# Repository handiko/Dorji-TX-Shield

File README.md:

# Arduino UNO Shield for Dorji DRA818V/U Transmitter
Dorji DRA818V VHF transmitter module shield for Arduino UNO &amp; compatibles.
This Arduino shield is intended to used as an APRS Transmitter module based on Arduino UNO (see my Arduino APRS [GitHub page](https://handiko.github.io/Arduino-APRS/) or [GitHub repo](https://github.com/handiko/Arduino-APRS). In this version (v.1.0), this board only support low power mode since high power will demand more current and this board only powered from 5V pin of the Arduino (It doesn't obtain power from Arduino Vin pin, yet).

## Photos

## Pinout

_Please note that in order to use PIN 8-11 as Serial Data lines, you need to use **SoftwareSerial** library._

## Schematic

## TODO
* Adding Silkscreen layer
* Adding ISP port capability
* Adding RX capability (maybe in a different repo..?)
* ...

## Acknowledgements
* Djoko Marjono Susilo - YB1TJ
* Adafruit Proto Shield PCB [GitHub page](https://github.com/adafruit/Adafruit-Proto-Shield-PCB)

## Contributing
1. Fork it [https://github.com/handiko/Dorji-TX-Shield/fork](https://github.com/handiko/Dorji-TX-Shield/fork)
2. Create new branch (`git checkout -b add-blah-blah`)
3. Do some editing / create new feature
4. Commit your works (`git commit -m "Adding some blah blah blah.."`)
5. Push to the branch (`git push -u origin add-blah-blah`)
6. Create a new Pull Request

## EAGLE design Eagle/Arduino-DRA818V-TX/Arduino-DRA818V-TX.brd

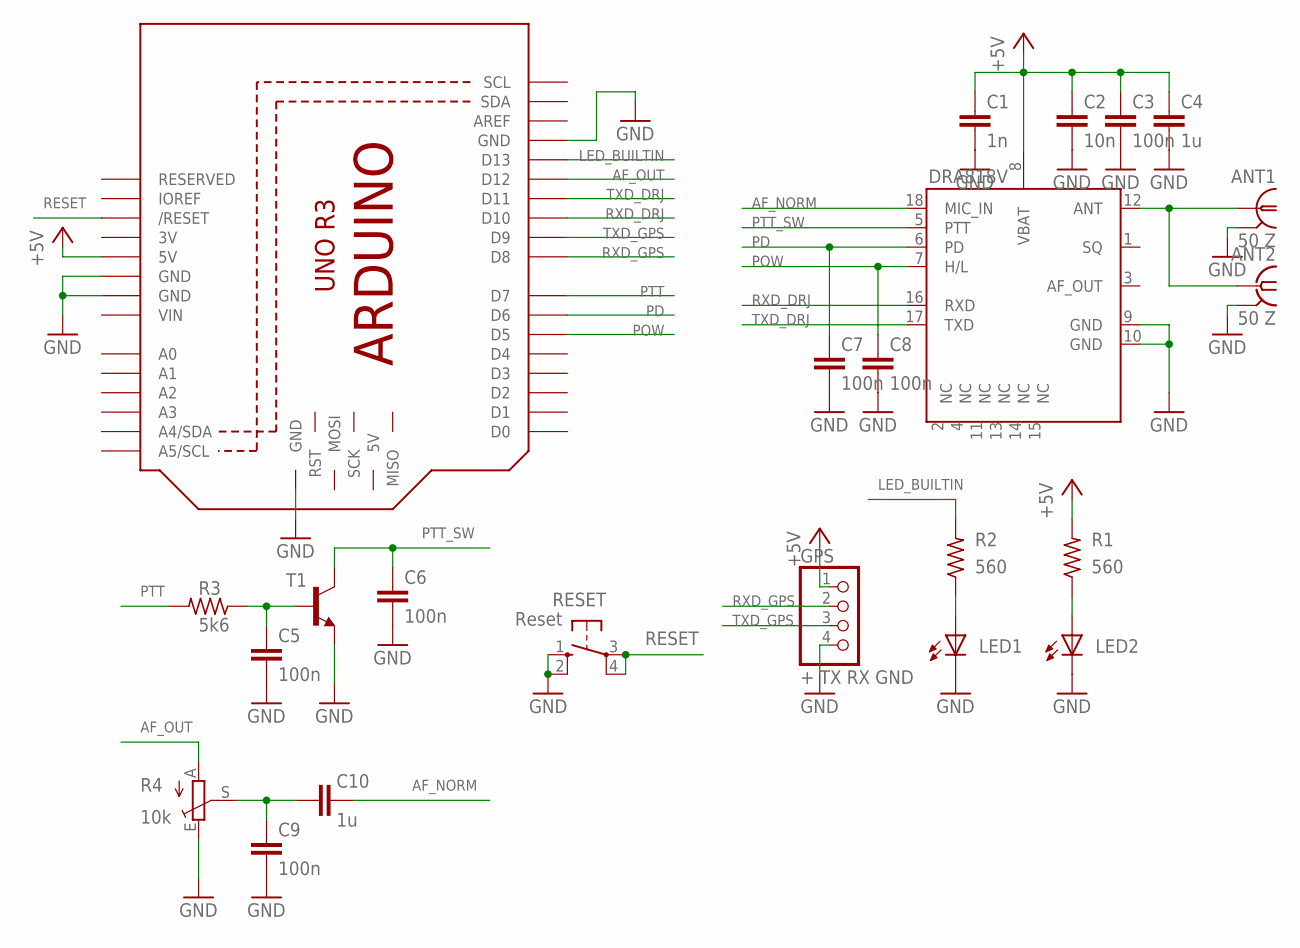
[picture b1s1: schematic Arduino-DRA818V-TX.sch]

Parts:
ANT1: 50 Z; LTI-SASF54GT
ANT2: 50 Z; J502-ND-142-0701-801/806
C1: 1n; C0805
C2: 10n; C0805
C3, C5, C6, C7, C8, C9: 100n; C0805
C4, C10: 1u; C0805
DRA818V: DRA818A
GPS: + TX RX GND; 1X04
LED1, LED2: LED3MM
M1: ARDUINO_R3_ICSP; ARDUINOR3_ICSP
R1, R2: 560; R0805
R3: 5k6; R0805
R4: 10k; CA6V
RESET: Reset; B3F-10XX
T1: MMBT3904LT1-NPN-SOT23-BEC; SOT23-BEC

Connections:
3V: M1.3V
+5V: C1.1, C2.1, C3.1, C4.1, DRA818V.8 (VBAT), GPS.1, M1.5V, R1.2
AF_NORM: C10.2, DRA818V.18 (MIC_IN)
AF_OUT: M1.D12, R4.A
GND: ANT1.2, ANT1.3 (2), ANT1.4 (2), ANT1.5 (2), ANT2.G@1 (2), ANT2.G@2 (2), ANT2.G@3 (2), ANT2.G@4 (2), C1.2, C2.2, C3.2, C4.2, C5.2, C6.2, C7.2, C8.2, C9.2, DRA818V.9 (GND), DRA818V.10 (GND), GPS.4, LED1.K (C), LED2.K (C), M1.GND, M1.GND@1 (GND), M1.GND@2 (GND), M1.GND@3 (GND), R4.E, RESET.1 (S), RESET.2 (S1), T1.E
LED_BUILTIN: M1.D13, R2.2
unnamed: ANT1.1, ANT2.1, DRA818V.12 (ANT)
unnamed: C5.1, R3.1, T1.B
unnamed: LED1.A, R2.1
unnamed: C9.1, C10.1, R4.S
unnamed: LED2.A, R1.1
PD: C7.1, DRA818V.6 (PD), M1.D6
POW: C8.1, DRA818V.7 (H/L), M1.D5
PTT: M1.D7, R3.2
PTT_SW: C6.1, DRA818V.5 (PTT), T1.C
RESET: M1.RESET (/RESET), RESET.3, RESET.4 (P1)
RXD_DRJ: DRA818V.16 (RXD), M1.D10
RXD_GPS: GPS.2, M1.D8
TXD_DRJ: DRA818V.17 (TXD), M1.D11
TXD_GPS: GPS.3, M1.D9
VIN: M1.VIN

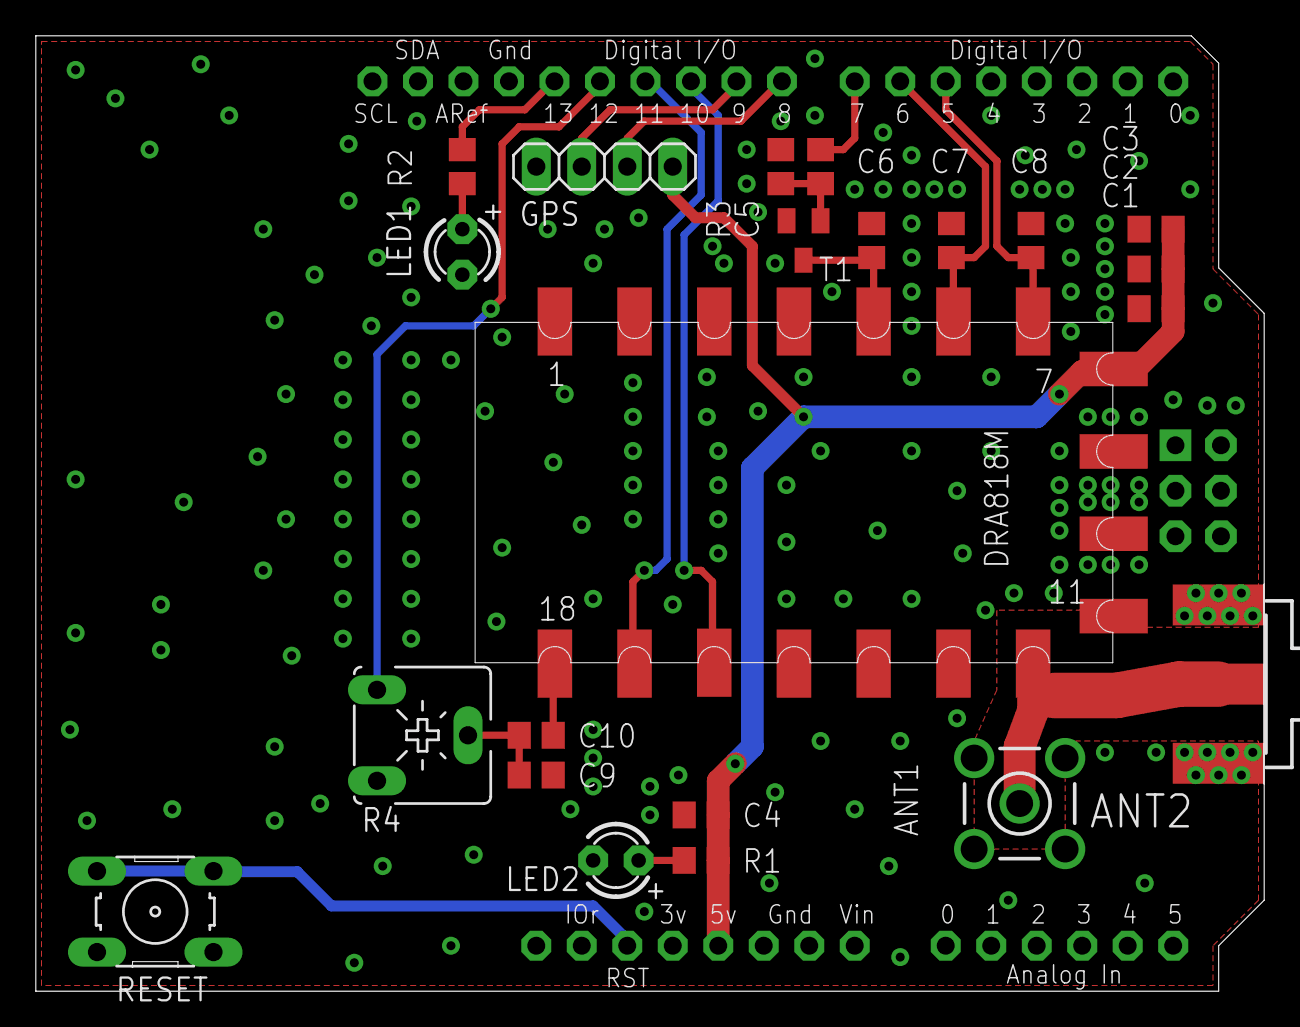
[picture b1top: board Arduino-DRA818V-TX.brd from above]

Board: 2 copper layers, 68.6 x 53.3 mm, 23 parts (0 on the bottom side), 19 nets.

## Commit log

2019-01-03 Rearrange folders
2019-01-03 Adding DRU
2019-01-03 Adding CAM
2019-01-03 Create LICENSE
2019-01-03 Adding pics
2019-01-03 Adding gitignore
2019-01-04 Adding Dorji Library
2019-01-04 Polygon re-pour
2019-01-04 Adding SCH PDF
2019-01-04 Adding Eagle Template
2019-01-04 Generate Gerber
2019-01-04 Adding Eagle SCH Template
2019-01-04 Adding BRD Template
2019-01-04 Change Info
2019-01-04 Generate Gerber files
2019-01-05 Using 0805 SMDs
2019-01-05 Generate SCH pdf
2019-01-05 Adding board view pic
2019-01-05 Recompile
2019-01-05 Update Pics
2019-01-13 Set theme jekyll-theme-tactile
2019-01-13 Set theme jekyll-theme-cayman
2019-01-14 replacing table with ss
2020-04-28 Set theme jekyll-theme-dinky
